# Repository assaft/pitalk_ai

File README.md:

# Introduction
This MD idescribes the creation of a device for recording, sending, receiving and playing vocal messages. 

## Device Goal
Enable easy voice messaging between kids. One click to start/end recording, one click to play an incoming. 

## Device Components
* Touch screen
* Microphone
* Speaker
* Amplifier
* System on chip - raspberry pi.
* Button with light
* PCB board, header cables, enclosure 

## Typical Use Case
Using the touch screen, user A can initiate a recording of a message to a particular pre-configured friend - user B. The microphone is used for the recording and a file is saved. Once user A presses to finish the recording, the file will be sent over the internet (using a Wifi connection), and reach the device of the recipient - user B. User B's device screen will show that there is an incoming message that hasn't been heard. Once user B presses on the screen to play it, the amplifier and speaker will be used to play it. 

# Requirements

## Functional Requirements
* A user can record a new message and send it to one of his/her friends. 
* A user can browse old messages he/she received and listen to them.
* A user can have a custom different list of friends - each user a different list 
* The list of friends per user should be editable.

## System Requirements
* The device should support reboot, shut down, turn on
* The device should have a Wifi access point mode so smartphones can connect to itto configure the Wifi network.

## Package Engineering Requirements
* The device should be packaged in a compact box
* The device should only have one external connection for power
* The screen, speaker, microphone and button should be front facing.
* The micro USB power should be side-facing.
* The comopnents should be mounted to the top or sides of the box, not to the bottom.
* The bottom should be openable using screws, giving access to all components inside.
* The raspberry pi should be attached on one of the sides to allow easy access to the screen, speaker, microphone and button.
* A custom PCB board should be used to simplify connectivity and maintenance
* The PCB should connect to the Raspberry Pi GPIO interface using a
  2×20 male pin header.

## PCB Board requirements
* The board should not include the amplifier - it should include a female socket for the amplifier to be connected to it using a male header that was soldered to it. 
* The board should not include the microphone because the microphone is attached to the front of the device. The microphone will have pin header soldered to it.
* there should be board connectors on the pcb for connecting it to the microphone, speaker, button and screen; the screen connector should be keyed/locking.

# Components

## Models
1. Controller: Raspberry Pi Zero 2W
2. Screen: Waveshare 2 inch Capacitive Touch Display Module (ST7789T3, CST816D)
3. Speaker: Gikfun 2 inch 4Ohm 3W Full Range Audio Speaker Stereo Woofer Loudspeaker
4. Amplifier: Max98357 I2S 3W Class D Amplifier
5. Microphone: INMP441 Omnidirectional Microphone attached over a Perfboard PCB of 2cm x 2cm
7. Button: momentary push button with led light

## Dimensions

| Component | Length | Width | Depth / Thickness | Notes |
|-----------|--------|-------|-------------------|-------|
| Raspberry Pi Zero 2W | 65 mm | 30 mm | ~5 mm | Board only; add ~2 mm for protruding micro-SD card |
| Waveshare 2" Capacitive Touch LCD (ST7789T3 / CST816D) | 58.8 mm | 37.1 mm | ~4 mm | PCB size; active display area is 40.8 × 30.6 mm |
| Gikfun 2" 4Ω 3W Speaker | 52.6 mm | 52.6 mm | 30 mm | Square frame |
| MAX98357 I2S Class-D Amplifier (breakout) | 19.4 mm | 17.8 mm | 3 mm | Adafruit-style breakout board |
| INMP441 Microphone (on 20 × 20 mm perfboard) | 20 mm | 20 mm | ~11 mm | Perfboard size per design spec; sensor itself is 4.7 × 3.8 × 1 mm |
| Momentary Push Button with LED | Ø 16–22 mm | — | ~39 mm | Circular; diameter depends on selected model (common: 16 mm or 22 mm panel cutout) |

# Box Arrangement

Two candidate front-face layouts. Scale: 1 char ≈ 5 mm.

## Layout 1 — Portrait (80 × 155 mm)

Screen on top, speaker in the middle, mic and button at the bottom.

```
╔══════════════════╗
║                  ║
║  ┌────────────┐  ║
║  │            │  ║
║  │   SCREEN   │  ║  58.8 × 37.1 mm
║  │            │  ║
║  └────────────┘  ║
║                  ║
║   ┌──────────┐   ║
║   │ ·  ·  ·  │   ║
║   │  ·  ·  · │   ║  52.6 × 52.6 mm
║   │ ·  ·  ·  │   ║
║   │  ·  ·  · │   ║
║   └──────────┘   ║
║                  ║
║   ◎         ◉    ║
║   mic       btn  ║
╚══════════════════╝
     80 × 155 mm
```

USB-C on the right side.

## Layout 4 — Landscape (150 × 80 mm)

Speaker on the left, screen on the right, mic and button below the screen.

```
╔══════════════════════════════════════╗
║                                      ║
║  ┌────────────┐  ┌────────────┐      ║
║  │ ·  ·  ·  · │  │            │      ║
║  │  ·  ·  ·   │  │   SCREEN   │      ║  58.8 × 37.1 mm
║  │ ·  ·  ·  · │  │            │      ║
║  │  ·  ·  ·   │  └────────────┘      ║
║  └────────────┘       ◎    ◉         ║
║                      mic   btn       ║
╚══════════════════════════════════════╝
  52.6 × 52.6 mm          150 × 80 mm
```

USB-C on the bottom edge (side of box). Button centered below screen, mic to its left.

## Internal Layout

### View from bottom

### View from the side

# PCB Design

Board: **76 mm × 58 mm**, four-layer, 1.6 mm FR4:

1. `F.Cu` — connector escapes and signals
2. `In1.Cu` — continuous ground plane
3. `In2.Cu` — secondary signal routing
4. `B.Cu` — signals and power

The authoritative wiring specification is [`pcb/pcb.md`](pcb/pcb.md). The
KiCad board is [`pcb/kicad/pitalk.kicad_pcb`](pcb/kicad/pitalk.kicad_pcb).
The matching schematic is
[`pcb/kicad/pitalk.kicad_sch`](pcb/kicad/pitalk.kicad_sch).

Regenerate it with:

```sh
.venv/bin/python pcb/kicad/build.py
.venv/bin/python pcb/kicad/build_schematic.py
```

## Connectors

| Ref | Footprint | Function |
|-----|-----------|----------|
| J1 | 2×20 2.54 mm male pin header | Raspberry Pi Zero 2W GPIO |
| J2 | JST GH SM15B 1.25 mm 1×15 male side-entry header | Waveshare 2" touch display |
| J3 | 1×7 2.54 mm female socket | MAX98357A amplifier module |
| J4, J5 | 1×3 2.54 mm male headers | INMP441 microphone |
| J6 | 1×4 2.54 mm male header | Momentary button + LED |

## GPIO Assignments (Raspberry Pi Zero 2W)

| Pin | GPIO | Net | Description |
|-----|------|-----|-------------|
| 1, 17 | 3V3 | +3V3 | Power |
| 2, 4 | 5V | +5V | Power (amp) |
| 3 | GPIO2 | I2C_SDA | Touch screen SDA |
| 5 | GPIO3 | I2C_SCL | Touch screen SCL |
| 7 | GPIO4 | TOUCH_INT | Touch interrupt |
| 12 | GPIO18 | I2S_BCLK | I2S bit clock (amp + mic) |
| 13 | GPIO27 | DISP_RST | Display reset |
| 15 | GPIO22 | BTN_SW | Button input |
| 19 | GPIO10 | SPI_MOSI | Display data |
| 22 | GPIO25 | DISP_DC | Display data/command |
| 23 | GPIO11 | SPI_SCLK | Display clock |
| 24 | GPIO8 | SPI_CE0 | Display chip select |
| 32 | GPIO12 | DISP_BL | Backlight PWM |
| 33 | GPIO13 | GPIO13 | LED drive (→ R1 → BTN_LED) |
| 35 | GPIO19 | I2S_LRCLK | I2S LR clock (amp + mic) |
| 38 | GPIO20 | I2S_DIN | I2S data from mic → RPi |
| 40 | GPIO21 | I2S_DOUT | I2S data RPi → amp |

## Passives

| Ref | Value | Purpose |
|-----|-------|---------|
| R1 | 330 Ω 0402 | BTN_LED current limiter (GPIO13 → LED) |
| C1 | 100 nF 0402 | +3V3 decoupling |
| C2 | 100 nF 0402 | +5V decoupling |

# Software code

# Todos 
* ~~Adding the component dimensions - width, height, depth - see section above.~~
* ~~Creating the box arrangment for organizing the components in a box - see section above.~~
* ~~Create a PCB board to simplify connections and maintenance - see section above.~~
* Writing the software for implementing the service.

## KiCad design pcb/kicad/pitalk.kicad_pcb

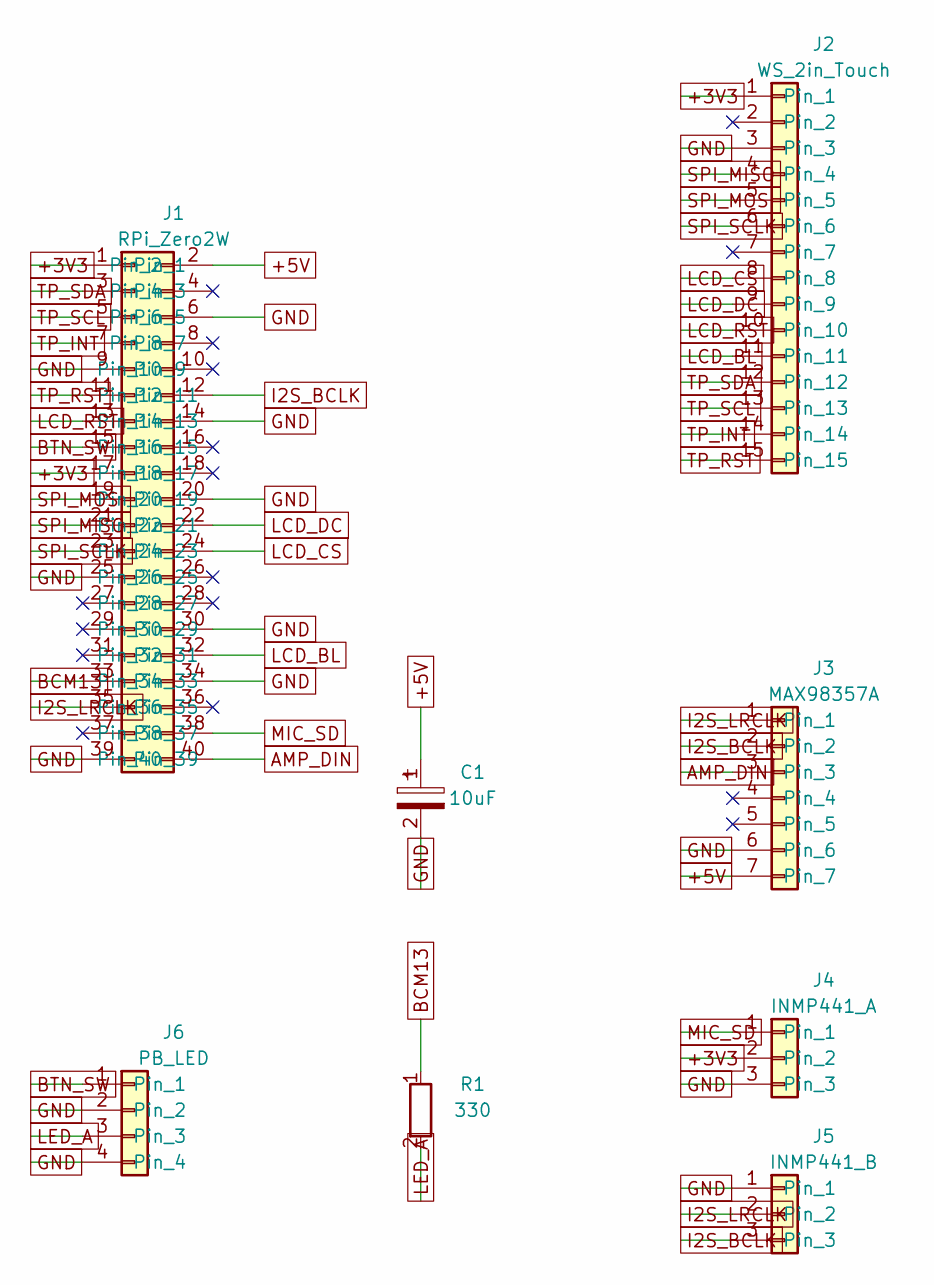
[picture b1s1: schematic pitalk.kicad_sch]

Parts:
C1: 10uF; CP_Radial_D5.0mm_P2.50mm
J1: RPi_Zero2W; PinHeader_2x20_P2.54mm_Vertical
J2: WS_2in_Touch; JST_GH_SM15B-GHS-TB_1x15-1MP_P1.25mm_Horizontal
J3: MAX98357A; PinSocket_1x07_P2.54mm_Vertical
J4: INMP441_A; PinHeader_1x03_P2.54mm_Vertical
J5: INMP441_B; PinHeader_1x03_P2.54mm_Vertical
J6: PB_LED; PinHeader_1x04_P2.54mm_Vertical
R1: 330; R_Axial_DIN0207_L6.3mm_D2.5mm_P10.16mm_Horizontal

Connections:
+3V3: J1.1, J1.17, J2.1, J4.2
+5V: C1.1, J1.2, J3.7
AMP_DIN: J1.40, J3.3
BCM13: J1.33, R1.1
BTN_SW: J1.15, J6.1
GND: C1.2, J1.6, J1.9, J1.14, J1.20, J1.25, J1.30, J1.34, J1.39, J2.3, J3.6, J4.3, J5.1, J6.2, J6.4
I2S_BCLK: J1.12, J3.2, J5.3
I2S_LRCLK: J1.35, J3.1, J5.2
LCD_BL: J1.32, J2.11
LCD_CS: J1.24, J2.8
LCD_DC: J1.22, J2.9
LCD_RST: J1.13, J2.10
LED_A: J6.3, R1.2
MIC_SD: J1.38, J4.1
SPI_MISO: J1.21, J2.4
SPI_MOSI: J1.19, J2.5
SPI_SCLK: J1.23, J2.6
TP_INT: J1.7, J2.14
TP_RST: J1.11, J2.15
TP_SCL: J1.5, J2.13
TP_SDA: J1.3, J2.12

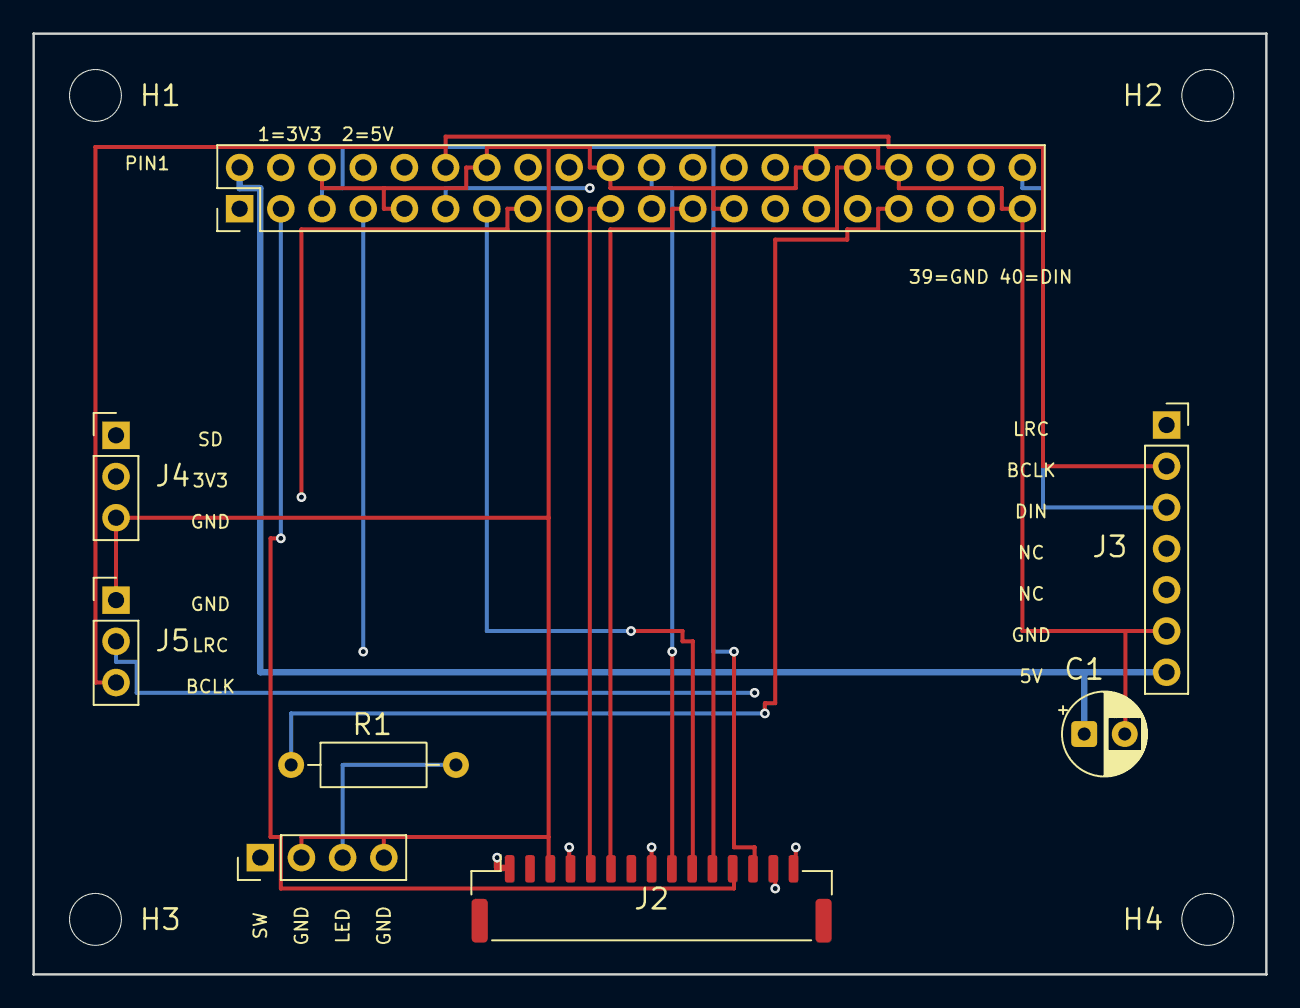
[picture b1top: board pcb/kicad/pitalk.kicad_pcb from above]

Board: 4 copper layers, 76.0 x 58.0 mm, 12 parts (0 on the bottom side), 21 nets.

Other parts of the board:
H1, H2, H3, H4: M3; MountingHole_3.2mm_M3

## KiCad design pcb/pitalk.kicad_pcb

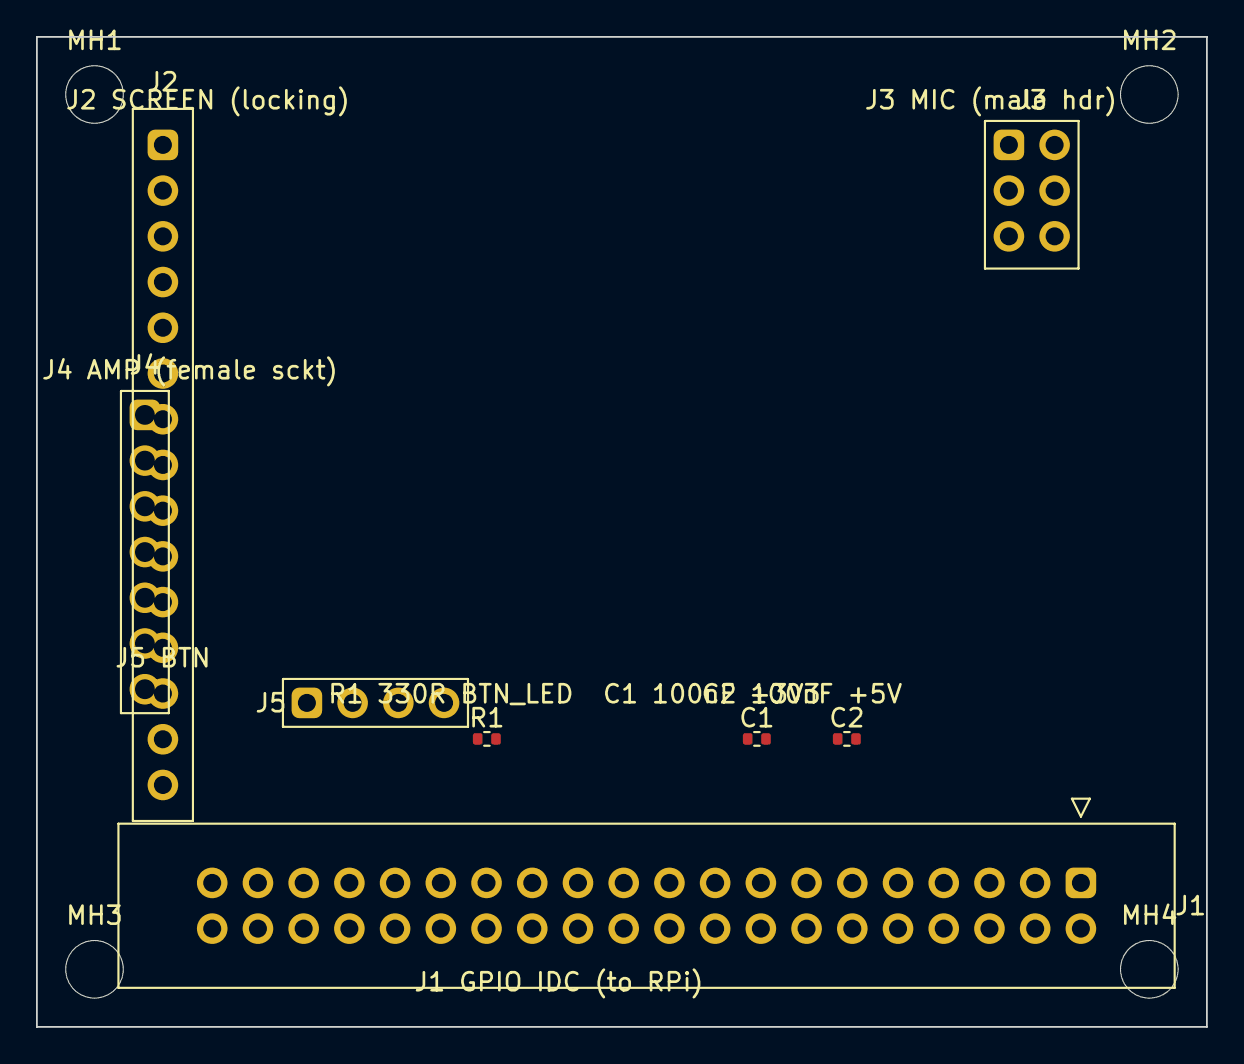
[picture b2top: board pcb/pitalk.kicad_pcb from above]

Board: 2 copper layers, 65.0 x 55.0 mm, 12 parts (0 on the bottom side), 19 nets, no tracks yet.

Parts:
C1, C2: 100nF; C_0402_1005Metric
J1: RPi_GPIO_40pin_IDC; IDC-Header_2x20_P2.54mm_Vertical
J2: Screen_Waveshare_2in_Molex_KK_254; Molex_KK-254_AE-6410-15A_1x15_P2.54mm_Vertical
J3: Mic_INMP441_Male_Header; PinHeader_2x03_P2.54mm_Vertical
J4: External_MAX98357A_Amp_Female; PinSocket_1x07_P2.54mm_Vertical
J5: Button_LED; PinHeader_1x04_P2.54mm_Vertical
MH1, MH2, MH3, MH4: MountingHole_3.2mm_M3
R1: 330R; R_0402_1005Metric

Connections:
+3V3: C1.1, J1.1, J1.17, J2.2, J2.4, J2.15, J3.1, J4.3
+5V: C2.1, J1.2, J1.4, J4.1
BTN_LED: J5.3, R1.2
BTN_SW: J1.15, J5.1
DISP_BL: J1.32, J2.13
DISP_DC: J1.22, J2.8
DISP_RST: J1.13, J2.9
GND: C1.2, C2.2, J1.6, J1.9, J1.14, J1.20, J1.25, J1.30, J1.34, J1.39, J2.1, J2.3, J2.14, J3.3, J3.5, J4.2, J4.4, J5.2, J5.4
GPIO13: J1.33, R1.1
I2C_SCL: J1.5, J2.11
I2C_SDA: J1.3, J2.10
I2S_BCLK: J1.12, J3.2, J4.6
I2S_DIN: J1.38, J3.6
I2S_DOUT: J1.40, J4.5
I2S_LRCLK: J1.35, J3.4, J4.7
SPI_CE0: J1.24, J2.7
SPI_MOSI: J1.19, J2.5
SPI_SCLK: J1.23, J2.6
TOUCH_INT: J1.7, J2.12

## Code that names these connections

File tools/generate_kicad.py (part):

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GPIO assignments (Raspberry Pi Zero 2W):
  Pin 1/17  3.3V       → +3V3
  Pin 2/4   5V         → +5V
  Pin 3     GPIO2 SDA  → I2C_SDA  (touch screen)
  Pin 5     GPIO3 SCL  → I2C_SCL  (touch screen)
  Pin 7     GPIO4      → TOUCH_INT
  Pin 12    GPIO18     → I2S_BCLK (amp BCLK + mic SCK)
  Pin 13    GPIO27     → DISP_RST
  Pin 15    GPIO22     → BTN_SW
  Pin 19    GPIO10     → SPI_MOSI (screen)
  Pin 22    GPIO25     → DISP_DC
  Pin 23    GPIO11     → SPI_SCLK (screen)
  Pin 24    GPIO8      → SPI_CE0  (screen)
  Pin 32    GPIO12     → DISP_BL  (backlight PWM)
  Pin 33    GPIO13     → GPIO13   (→ R1 → BTN_LED)
  Pin 35    GPIO19     → I2S_LRCLK (amp LRC + mic WS)
  Pin 38    GPIO20     → I2S_DIN  (mic SD → RPi)
  Pin 40    GPIO21     → I2S_DOUT (RPi → amp DIN)
  GND: pins 6,9,14,20,25,30,34,39
"""
import uuid
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    (15, "I2S_DIN"),
    (16, "I2S_DOUT"),
    (17, "BTN_SW"),
    (18, "GPIO13"),
    (19, "BTN_LED"),
]
NETNAME = {n: name for n, name in NETS}
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          (stroke (width 0) (type default)) (fill (type pin_numbers_background)))
        ;; — odd pins (left column, GPIO signals) —
        (pin passive (at -5.08  50.80 0) (length 3.81) (name "3V3"      (effects (font (size 1.27 1.27)))) (number "1"  (effects (font (size 1.27 1.27)))))
        (pin passive (at -5.08  45.72 0) (length 3.81) (name "I2C_SDA"  (effects (font (size 1.27 1.27)))) (number "3"  (effects (font (size 1.27 1.27)))))
        (pin passive (at -5.08  40.64 0) (length 3.81) (name "I2C_SCL"  (effects (font (size 1.27 1.27)))) (number "5"  (effects (font (size 1.27 1.27)))))
        (pin passive (at -5.08  35.56 0) (length 3.81) (name "TOUCH_INT" (effects (font (size 1.27 1.27)))) (number "7"  (effects (font (size 1.27 1.27)))))
        (pin passive (at -5.08  30.48 0) (length 3.81) (name "GND"      (effects (font (size 1.27 1.27)))) (number "9"  (effects (font (size 1.27 1.27)))))
        (pin passive (at -5.08  25.40 0) (length 3.81) (name "NC"       (effects (font (size 1.27 1.27)))) (number "11" (effects (font (size 1.27 1.27)))))
        (pin passive (at -5.08  20.32 0) (length 3.81) (name "DISP_RST" (effects (font (size 1.27 1.27)))) (number "13" (effects (font (size 1.27 1.27)))))
        (pin passive (at -5.08  15.24 0) (length 3.81) (name "BTN_SW"   (effects (font (size 1.27 1.27)))) (number "15" (effects (font (size 1.27 1.27)))))
        (pin passive (at -5.08  10.16 0) (length 3.81) (name "3V3"      (effects (font (size 1.27 1.27)))) (number "17" (effects (font (size 1.27 1.27)))))
        (pin passive (at -5.08   5.08 0) (length 3.81) (name "SPI_MOSI" (effects (font (size 1.27 1.27)))) (number "19" (effects (font (size 1.27 1.27)))))
        (pin passive (at -5.08   0.00 0) (length 3.81) (name "NC"       (effects (font (size 1.27 1.27)))) (number "21" (effects (font (size 1.27 1.27)))))
        (pin passive (at -5.08  -5.08 0) (length 3.81) (name "SPI_SCLK" (effects (font (size 1.27 1.27)))) (number "23" (effects (font (size 1.27 1.27)))))
        (pin passive (at -5.08 -10.16 0) (length 3.81) (name "GND"      (effects (font (size 1.27 1.27)))) (number "25" (effects (font (size 1.27 1.27)))))
        (pin passive (at -5.08 -15.24 0) (length 3.81) (name "NC"       (effects (font (size 1.27 1.27)))) (number "27" (effects (font (size 1.27 1.27)))))
        (pin passive (at -5.08 -20.32 0) (length 3.81) (name "NC"       (effects (font (size 1.27 1.27)))) (number "29" (effects (font (size 1.27 1.27)))))
        (pin passive (at -5.08 -25.40 0) (length 3.81) (name "NC"       (effects (font (size 1.27 1.27)))) (number "31" (effects (font (size 1.27 1.27)))))
        (pin passive (at -5.08 -30.48 0) (length 3.81) (name "BTN_LED"  (effects (font (size 1.27 1.27)))) (number "33" (effects (font (size 1.27 1.27)))))
        (pin passive (at -5.08 -35.56 0) (length 3.81) (name "I2S_LRCLK"(effects (font (size 1.27 1.27)))) (number "35" (effects (font (size 1.27 1.27)))))
        (pin passive (at -5.08 -40.64 0) (length 3.81) (name "NC"       (effects (font (size 1.27 1.27)))) (number "37" (effects (font (size 1.27 1.27)))))
        (pin passive (at -5.08 -45.72 0) (length 3.81) (name "GND"      (effects (font (size 1.27 1.27)))) (number "39" (effects (font (size 1.27 1.27)))))
        ;; — even pins (right column, power + audio) —
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        (pin passive (at  8.89  40.64 180) (length 3.81) (name "GND"       (effects (font (size 1.27 1.27)))) (number "6"  (effects (font (size 1.27 1.27)))))
        (pin passive (at  8.89  35.56 180) (length 3.81) (name "NC"        (effects (font (size 1.27 1.27)))) (number "8"  (effects (font (size 1.27 1.27)))))
        (pin passive (at  8.89  30.48 180) (length 3.81) (name "NC"        (effects (font (size 1.27 1.27)))) (number "10" (effects (font (size 1.27 1.27)))))
        (pin passive (at  8.89  25.40 180) (length 3.81) (name "I2S_BCLK" (effects (font (size 1.27 1.27)))) (number "12" (effects (font (size 1.27 1.27)))))
        (pin passive (at  8.89  20.32 180) (length 3.81) (name "GND"       (effects (font (size 1.27 1.27)))) (number "14" (effects (font (size 1.27 1.27)))))
        (pin passive (at  8.89  15.24 180) (length 3.81) (name "NC"        (effects (font (size 1.27 1.27)))) (number "16" (effects (font (size 1.27 1.27)))))
        (pin passive (at  8.89  10.16 180) (length 3.81) (name "NC"        (effects (font (size 1.27 1.27)))) (number "18" (effects (font (size 1.27 1.27)))))
        (pin passive (at  8.89   5.08 180) (length 3.81) (name "GND"       (effects (font (size 1.27 1.27)))) (number "20" (effects (font (size 1.27 1.27)))))
        (pin passive (at  8.89   0.00 180) (length 3.81) (name "DISP_DC"   (effects (font (size 1.27 1.27)))) (number "22" (effects (font (size 1.27 1.27)))))
        (pin passive (at  8.89  -5.08 180) (length 3.81) (name "SPI_CE0"   (effects (font (size 1.27 1.27)))) (number "24" (effects (font (size 1.27 1.27)))))
        (pin passive (at  8.89 -10.16 180) (length 3.81) (name "NC"        (effects (font (size 1.27 1.27)))) (number "26" (effects (font (size 1.27 1.27)))))
        (pin passive (at  8.89 -15.24 180) (length 3.81) (name "NC"        (effects (font (size 1.27 1.27)))) (number "28" (effects (font (size 1.27 1.27)))))
        (pin passive (at  8.89 -20.32 180) (length 3.81) (name "GND"       (effects (font (size 1.27 1.27)))) (number "30" (effects (font (size 1.27 1.27)))))
        (pin passive (at  8.89 -25.40 180) (length 3.81) (name "DISP_BL"   (effects (font (size 1.27 1.27)))) (number "32" (effects (font (size 1.27 1.27)))))
        (pin passive (at  8.89 -30.48 180) (length 3.81) (name "GND"       (effects (font (size 1.27 1.27)))) (number "34" (effects (font (size 1.27 1.27)))))
        (pin passive (at  8.89 -35.56 180) (length 3.81) (name "NC"        (effects (font (size 1.27 1.27)))) (number "36" (effects (font (size 1.27 1.27)))))
        (pin passive (at  8.89 -40.64 180) (length 3.81) (name "I2S_DIN"   (effects (font (size 1.27 1.27)))) (number "38" (effects (font (size 1.27 1.27)))))
        (pin passive (at  8.89 -45.72 180) (length 3.81) (name "I2S_DOUT"  (effects (font (size 1.27 1.27)))) (number "40" (effects (font (size 1.27 1.27)))))
      )
    )

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      (symbol "Conn_01x04_Button_1_1"
        (rectangle (start -1.27 5.715) (end 1.27 -5.715)
          (stroke (width 0) (type default)) (fill (type pin_numbers_background)))
        (pin passive (at -5.08  3.81 0) (length 3.81) (name "BTN_SW"  (effects (font (size 1.27 1.27)))) (number "1" (effects (font (size 1.27 1.27)))))
        (pin passive (at -5.08  1.27 0) (length 3.81) (name "GND"     (effects (font (size 1.27 1.27)))) (number "2" (effects (font (size 1.27 1.27)))))
        (pin passive (at -5.08 -1.27 0) (length 3.81) (name "BTN_LED" (effects (font (size 1.27 1.27)))) (number "3" (effects (font (size 1.27 1.27)))))
        (pin passive (at -5.08 -3.81 0) (length 3.81) (name "GND"     (effects (font (size 1.27 1.27)))) (number "4" (effects (font (size 1.27 1.27)))))
      )
    )
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    lx = 29.92
    LEFT_PINS = [
        (50.80, "+3V3",     "power",       "pwr_sym"),
        (45.72, "I2C_SDA",  "bidirectional", "glabel"),
        (40.64, "I2C_SCL",  "bidirectional", "glabel"),
        (35.56, "TOUCH_INT","input",        "glabel"),
        (30.48, "GND",      "power",       "pwr_sym"),
        (25.40, None,       None,          "noconn"),   # pin 11 NC
        (20.32, "DISP_RST", "output",      "glabel"),
        (15.24, "BTN_SW",   "input",       "glabel"),
        (10.16, "+3V3",     "power",       "pwr_sym"),
        ( 5.08, "SPI_MOSI", "output",      "glabel"),
        ( 0.00, None,       None,          "noconn"),   # pin 21 NC
        (-5.08, "SPI_SCLK", "output",      "glabel"),
        (-10.16,"GND",      "power",       "pwr_sym"),
        (-15.24, None,      None,          "noconn"),   # pin 27 NC
        (-20.32, None,      None,          "noconn"),   # pin 29 NC
        (-25.40, None,      None,          "noconn"),   # pin 31 NC
        (-30.48, "GPIO13",  "output",      "glabel"),
        (-35.56, "I2S_LRCLK","bidirectional","glabel"),
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
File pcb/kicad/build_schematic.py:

#!/usr/bin/env python3
"""Generate the PiTalk KiCad schematic from the verified PCB wiring."""

from copy import deepcopy
from pathlib import Path
import uuid

from kiutils.items.common import Effects, Font, Position
from kiutils.items.schitems import (
    Connection,
    GlobalLabel,
    NoConnect,
    SchematicSymbol,
    SymbolProjectInstance,
    SymbolProjectPath,
)
from kiutils.schematic import Schematic
from kiutils.symbol import SymbolLib


HERE = Path(__file__).resolve().parent
OUT = HERE / "pitalk.kicad_sch"
SYMLIB = Path("/Applications/KiCad/KiCad.app/Contents/SharedSupport/symbols")
PROJECT_UUID = str(uuid.uuid4())

COMPONENTS = [
    {
        "ref": "J1",
        "symbol": "Connector_Generic:Conn_02x20_Odd_Even",
        "value": "RPi_Zero2W",
        "footprint": "Connector_PinHeader_2.54mm:PinHeader_2x20_P2.54mm_Vertical",
        "at": (63.5, 85.09),
        "pins": {
            1: "+3V3", 2: "+5V", 3: "TP_SDA", 5: "TP_SCL", 6: "GND",
            7: "TP_INT", 9: "GND", 11: "TP_RST", 12: "I2S_BCLK",
            13: "LCD_RST", 14: "GND", 15: "BTN_SW", 17: "+3V3",
            19: "SPI_MOSI", 20: "GND", 21: "SPI_MISO", 22: "LCD_DC",
            23: "SPI_SCLK", 24: "LCD_CS", 25: "GND", 30: "GND",
            32: "LCD_BL", 33: "BCM13", 34: "GND", 35: "I2S_LRCLK",
            38: "MIC_SD", 39: "GND", 40: "AMP_DIN",
        },
    },
    {
        "ref": "J2",
        "symbol": "Connector_Generic:Conn_01x15",
        "value": "WS_2in_Touch",
        "footprint": "Connector_JST:JST_GH_SM15B-GHS-TB_1x15-1MP_P1.25mm_Horizontal",
        "at": (127.0, 63.5),
        "pins": {
            1: "+3V3", 3: "GND", 4: "SPI_MISO", 5: "SPI_MOSI",
            6: "SPI_SCLK", 8: "LCD_CS", 9: "LCD_DC", 10: "LCD_RST",
            11: "LCD_BL", 12: "TP_SDA", 13: "TP_SCL", 14: "TP_INT",
            15: "TP_RST",
        },
    },
    {
        "ref": "J3",
        "symbol": "Connector_Generic:Conn_01x07",
        "value": "MAX98357A",
        "footprint": "Connector_PinSocket_2.54mm:PinSocket_1x07_P2.54mm_Vertical",
        "at": (127.0, 114.3),
        "pins": {
            1: "I2S_LRCLK", 2: "I2S_BCLK", 3: "AMP_DIN",
            6: "GND", 7: "+5V",
        },
    },
    {
        "ref": "J4",
        "symbol": "Connector_Generic:Conn_01x03",
        "value": "INMP441_A",
        "footprint": "Connector_PinHeader_2.54mm:PinHeader_1x03_P2.54mm_Vertical",
        "at": (127.0, 139.7),
        "pins": {1: "MIC_SD", 2: "+3V3", 3: "GND"},
    },
    {
        "ref": "J5",
        "symbol": "Connector_Generic:Conn_01x03",
        "value": "INMP441_B",
        "footprint": "Connector_PinHeader_2.54mm:PinHeader_1x03_P2.54mm_Vertical",
        "at": (127.0, 154.94),
        "pins": {1: "GND", 2: "I2S_LRCLK", 3: "I2S_BCLK"},
    },
    {
        "ref": "J6",
        "symbol": "Connector_Generic:Conn_01x04",
        "value": "PB_LED",
        "footprint": "Connector_PinHeader_2.54mm:PinHeader_1x04_P2.54mm_Vertical",
        "at": (63.5, 144.78),
        "pins": {1: "BTN_SW", 2: "GND", 3: "LED_A", 4: "GND"},
    },
    {
        "ref": "R1",
        "symbol": "Device:R",
        "value": "330",
        "footprint": "Resistor_THT:R_Axial_DIN0207_L6.3mm_D2.5mm_P10.16mm_Horizontal",
        "at": (91.44, 144.78),
        "pins": {1: "BCM13", 2: "LED_A"},
    },
    {
        "ref": "C1",
        "symbol": "Device:C_Polarized",
        "value": "10uF",
        "footprint": "Capacitor_THT:CP_Radial_D5.0mm_P2.50mm",
        "at": (91.44, 114.3),
        "pins": {1: "+5V", 2: "GND"},
    },
]


def uid() -> str:
    return str(uuid.uuid4())


def load_symbols():
    libraries = {}
    for nickname, filename in (
        ("Connector_Generic", "Connector_Generic.kicad_sym"),
        ("Device", "Device.kicad_sym"),
    ):
        library = SymbolLib.from_file(SYMLIB / filename)
        libraries[nickname] = {symbol.entryName: symbol for symbol in library.symbols}
    return libraries


def pin_definitions(symbol):
    pins = {}
    for unit in symbol.units:
        for pin in unit.pins:
            pins[int(pin.number)] = pin
    return pins


def pin_position(component, pin):
    x, y = component["at"]
    # Symbol-library coordinates use positive Y upward; schematic sheet
    # coordinates use positive Y downward.
    return Position(x + pin.position.X, y - pin.position.Y)


def label_position(position, angle):
    distance = 5.08
    offsets = {
        0: (-distance, 0),
        90: (0, distance),
        180: (distance, 0),
        270: (0, -distance),
    }
    dx, dy = offsets[int(angle or 0) % 360]
    return Position(position.X + dx, position.Y + dy, angle or 0)


def property_copy(properties, key, value, x, y, hidden=False):
    prop = deepcopy(next(prop for prop in properties if prop.key == key))
    prop.value = value
    prop.position = Position(x, y, 0)
    prop.effects = Effects(font=Font(width=1.27, height=1.27), hide=hidden)
    prop.showName = False
    return prop


def main():
    libraries = load_symbols()
    schematic = Schematic.create_new()
    schematic.version = 20231120
    schematic.generator = "pitalk_schematic_build"
    schematic.uuid = PROJECT_UUID

    embedded = {}
    for component in COMPONENTS:
        nickname, name = component["symbol"].split(":")
        if component["symbol"] not in embedded:
            symbol = deepcopy(libraries[nickname][name])
            symbol.libId = component["symbol"]
            embedded[component["symbol"]] = symbol
            schematic.libSymbols.append(symbol)

        definition = embedded[component["symbol"]]
        pins = pin_definitions(definition)
        x, y = component["at"]
        pin_y = [pin_position(component, pin).Y for pin in pins.values()]
        if component["symbol"].startswith("Connector_Generic:"):
            ref_x = x + 3.81
            ref_y = min(pin_y) - 5.08
            value_x = ref_x
            value_y = ref_y + 2.54
        else:
            ref_x = x + 5.08
            ref_y = y - 2.54
            value_x = ref_x
            value_y = y
        symbol_uuid = uid()
        instance = SchematicSymbol(
            position=Position(x, y, 0),
            unit=1,
            inBom=True,
            onBoard=True,
            uuid=symbol_uuid,
        )
        instance.libId = component["symbol"]
        instance.properties = [
            property_copy(
                definition.properties, "Reference", component["ref"], ref_x, ref_y
            ),
            property_copy(
                definition.properties, "Value", component["value"], value_x, value_y
            ),
            property_copy(
                definition.properties, "Footprint", component["footprint"], x, y, hidden=True
            ),
            property_copy(definition.properties, "Datasheet", "~", x, y, hidden=True),
        ]
        instance.pins = {str(number): uid() for number in pins}
        instance.instances = [
            SymbolProjectInstance(
                name="pitalk",
                paths=[
                    SymbolProjectPath(
                        sheetInstancePath=f"/{PROJECT_UUID}",
                        reference=component["ref"],
                        unit=1,
                    )
                ],
            )
        ]
        schematic.schematicSymbols.append(instance)

        connected = component["pins"]
        for number, pin in pins.items():
            position = pin_position(component, pin)
            if number in connected:
                label_at = label_position(position, pin.position.angle)
                schematic.graphicalItems.append(
                    Connection(
                        type="wire",
                        points=[
                            Position(position.X, position.Y),
                            Position(label_at.X, label_at.Y),
                        ],
                        uuid=uid(),
                    )
                )
                schematic.globalLabels.append(
                    GlobalLabel(
                        text=connected[number],
                        shape="passive",
                        position=label_at,
                        effects=Effects(font=Font(width=1.27, height=1.27)),
                        uuid=uid(),
                    )
                )
            else:
                schematic.noConnects.append(NoConnect(position=position, uuid=uid()))

    schematic.to_file(OUT)
    print(f"wrote {OUT}")


if __name__ == "__main__":
    main()

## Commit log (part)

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2026-05-28 Add PCB design files
2026-05-28 Add KiCad PCB layout and 3D exports
2026-05-28 Add Blender-rendered KiCad PCB preview
2026-05-28 Fix KiCad PCB render camera
2026-05-28 Fix KiCad PCB render framing
2026-06-06 Move amplifier to external header
2026-06-26 Add KiCad PCB design artifacts
2026-06-26 Add connector pin labels to PCB silkscreen
2026-06-26 Regenerate PCB fabrication outputs
